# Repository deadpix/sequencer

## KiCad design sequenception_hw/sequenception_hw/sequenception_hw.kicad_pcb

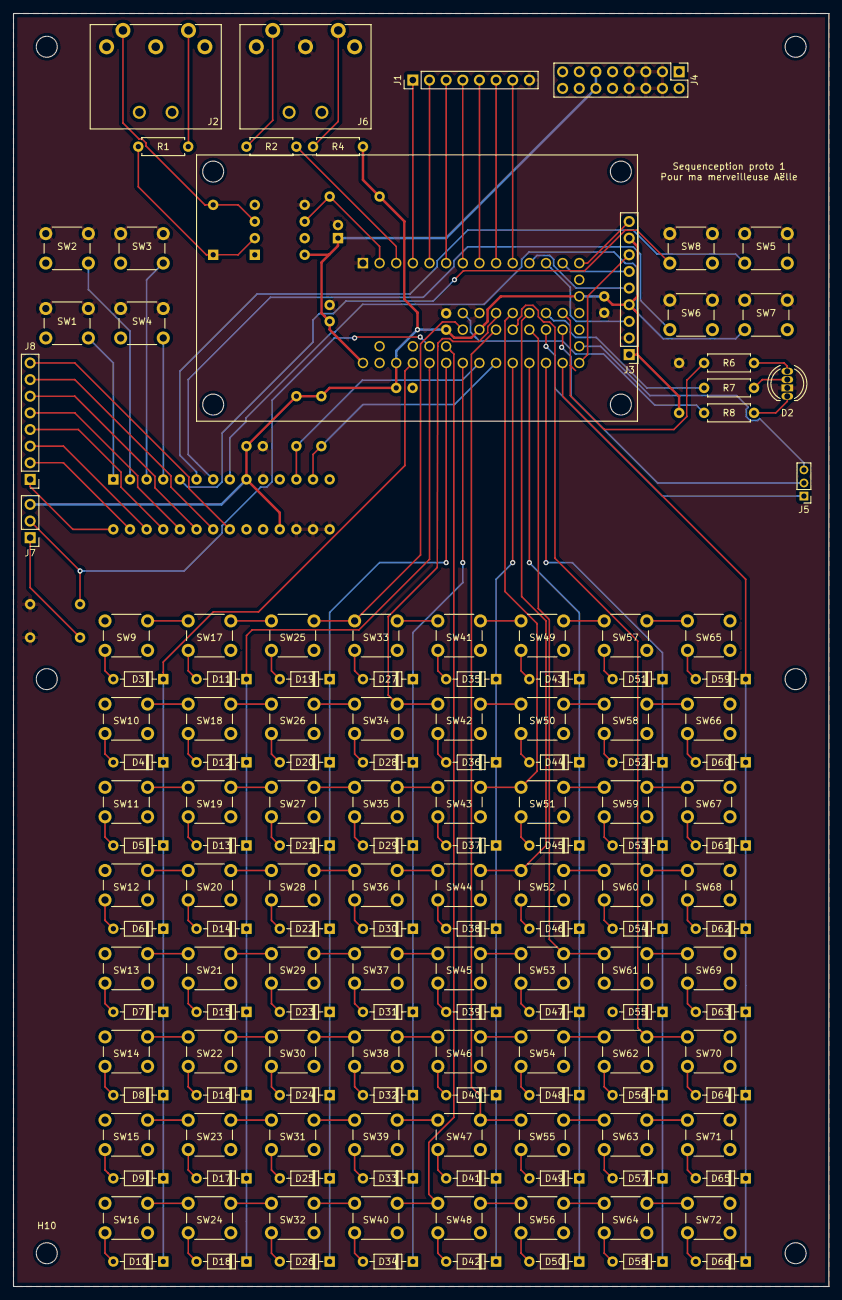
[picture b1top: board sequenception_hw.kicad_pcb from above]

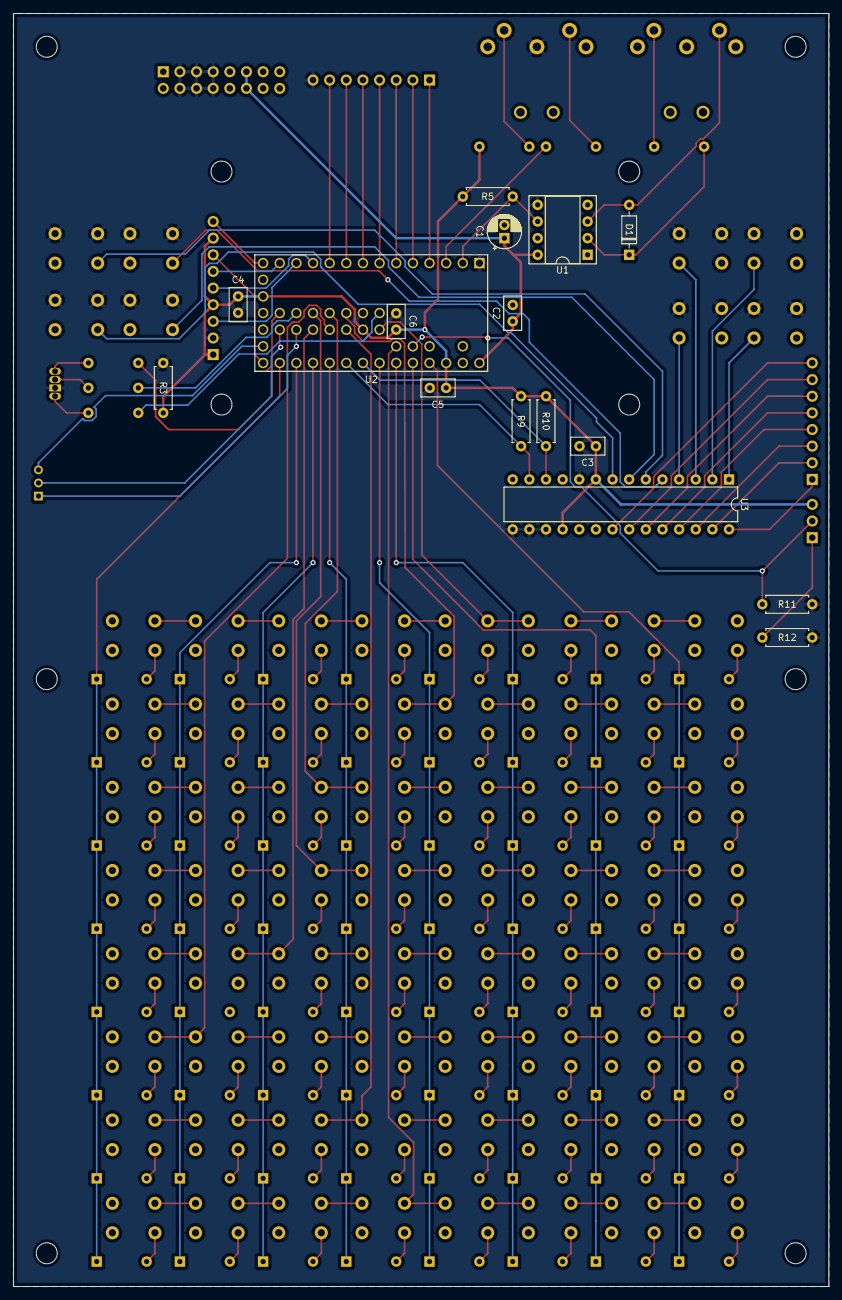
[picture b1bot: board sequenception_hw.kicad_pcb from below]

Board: 2 copper layers, 124.5 x 194.3 mm, 177 parts (16 on the bottom side), 131 nets.

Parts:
C1: 0.1uF; CP_Radial_D5.0mm_P2.00mm
C2, C3, C4, C5, C6: 0.1uF; C_Disc_D5.0mm_W2.5mm_P2.50mm
D1: 1N4148; D_DO-35_SOD27_P7.62mm_Horizontal
D2: LED_CRGB; LED_D5.0mm-4_RGB_common-cathode
D3, D4, D5, D6, D7, D8, D9, D10, D11, D12, D13, D14, D15, D16, D17, D18, D19, D20, D21, D22, D23, D24, D25, D26, D27, D28, D29, D30, D31, D32, D33, D34, D35, D36, D37, D38, D39, D40, D41, D42, D43, D44, D45, D46, D47, D48, D49, D50, D51, D52, D53, D54, D55, D56, D57, D58, D59, D60, D61, D62, D63, D64, D65, D66: D; D_DO-35_SOD27_P7.62mm_Horizontal
H1, H2, H3, H4, H5, H6, H7, H8, H9, H10: MountingHole; MountingHole_3.2mm_M3
J1, J8: Conn_01x08_Male; PinHeader_1x08_P2.54mm_Vertical
J2: MIDI_IN; SDS-50J
J3: Conn_01x09_Female; PinHeader_1x09_P2.54mm_Vertical
J4: Conn_02x08_Odd_Even; PinHeader_2x08_P2.54mm_Vertical
J5: Conn_01x03_Male; PinHeader_1x03_P2.00mm_Vertical
J6: MIDI_OUT; SDS-50J
J7: SOFTPOT_CONN; PinHeader_1x03_P2.54mm_Vertical
R1: 220; R_Axial_DIN0207_L6.3mm_D2.5mm_P7.62mm_Horizontal
R2, R4, R6, R7, R8: 47; R_Axial_DIN0207_L6.3mm_D2.5mm_P7.62mm_Horizontal
R3: 100; R_Axial_DIN0207_L6.3mm_D2.5mm_P7.62mm_Horizontal
R5: 470; R_Axial_DIN0207_L6.3mm_D2.5mm_P7.62mm_Horizontal
R9, R10: 4.7K; R_Axial_DIN0207_L6.3mm_D2.5mm_P7.62mm_Horizontal
R11, R12: R; R_Axial_DIN0207_L6.3mm_D2.5mm_P7.62mm_Horizontal
SW1, SW2, SW3, SW4, SW5, SW6, SW7, SW8, SW9, SW10, SW11, SW12, SW13, SW14, SW15, SW16, SW17, SW18, SW19, SW20, SW21, SW22, SW23, SW24, SW25, SW26, SW27, SW28, SW29, SW30, SW31, SW32, SW33, SW34, SW35, SW36, SW37, SW38, SW39, SW40, SW41, SW42, SW43, SW44, SW45, SW46, SW47, SW48, SW49, SW50, SW51, SW52, SW53, SW54, SW55, SW56, SW57, SW58, SW59, SW60, SW61, SW62, SW63, SW64, SW65, SW66, SW67, SW68, SW69, SW70, SW71, SW72: SW_Push; SW_PUSH_6mm
U1: 6N138; DIP-8_W7.62mm_Socket
U2: Teensy3.2-teensy; Teensy_32_test
U3: MCP23017_SP; DIP-28_W7.62mm

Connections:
+3V3: C3.1, C4.1, C5.1, C6.1, J3.1, J3.4, J3.8, J7.3, R3.2, R4.1, R5.2, R9.2, R10.1, U2.16, U2.31, U2.46, U3.9, U3.18
+5V: C1.1, C2.1, J4.11, J4.12, U1.8, U2.33
/BLUE: R6.2, U2.44
/DC_RS: J3.5, U2.11
/GPA0: J8.8, U3.21
/GPA1: J8.7, U3.22
/GPA2: J8.6, U3.23
/GPA3: J8.5, U3.24
/GPA4: J8.4, U3.25
/GPA5: J8.3, U3.26
/GPA6: J8.2, U3.27
/GPA7: J8.1, U3.28
/GREEN: R7.2, U2.43
/I2C_CLK: R10.2, U2.26, U3.12
/I2C_DATA: R9.1, U2.25, U3.13
/MAT_COL_0: D3.1, D4.1, D5.1, D6.1, D7.1, D8.1, D9.1, D10.1, U2.30
/MAT_COL_1: D11.1, D12.1, D13.1, D14.1, D15.1, D16.1, D17.1, D18.1, U2.29
/MAT_COL_2: D19.1, D20.1, D21.1, D22.1, D23.1, D24.1, D25.1, D26.1, U2.28
/MAT_COL_3: D27.1, D28.1, D29.1, D30.1, D31.1, D32.1, D33.1, D34.1, U2.27
/MAT_COL_4: D35.1, D36.1, D37.1, D38.1, D39.1, D40.1, D41.1, D42.1, U2.24
/MAT_COL_5: D43.1, D44.1, D45.1, D46.1, D47.1, D48.1, D49.1, D50.1, U2.23
/MAT_COL_6: D51.1, D52.1, D53.1, D54.1, D55.1, D56.1, D57.1, D58.1, U2.22
/MAT_COL_7: D59.1, D60.1, D61.1, D62.1, D63.1, D64.1, D65.1, D66.1, U2.21
/MAT_ROW_0: SW9.1, SW17.1, SW25.1, SW33.1, SW41.1, SW49.1, SW57.1, SW65.1, U2.51
/MAT_ROW_1: SW10.1, SW18.1, SW26.1, SW34.1, SW42.1, SW50.1, SW58.1, SW66.1, U2.40
/MAT_ROW_2: SW11.1, SW19.1, SW27.1, SW35.1, SW43.1, SW51.1, SW59.1, SW67.1, U2.41
/MAT_ROW_3: SW12.1, SW20.1, SW28.1, SW36.1, SW44.1, SW52.1, SW60.1, SW68.1, U2.42
/MAT_ROW_4: SW13.1, SW21.1, SW29.1, SW37.1, SW45.1, SW53.1, SW61.1, SW69.1, U2.48
/MAT_ROW_5: SW14.1, SW22.1, SW30.1, SW38.1, SW46.1, SW54.1, SW62.1, SW70.1, U2.49
/MAT_ROW_6: SW15.1, SW23.1, SW31.1, SW39.1, SW47.1, SW55.1, SW63.1, SW71.1, U2.50
/MAT_ROW_7: SW16.1, SW24.1, SW32.1, SW40.1, SW48.1, SW56.1, SW64.1, SW72.1, U2.37
/PIN2: J1.1, U2.4
/PIN3: J1.2, U2.5
/PIN4: J1.3, U2.6
/PIN5: J1.4, U2.7
/PIN6: J1.5, U2.8
/PIN7: J1.6, U2.9
/PIN8: J1.7, U2.10
/PIN10: J5.3, U2.19
/PIN11: J5.1, U2.47
/PIN12: J5.2, U2.45
/RED: R8.2, U2.38
/SP: J7.2, R11.1, U2.36
/SPI_CLK: J3.7, U2.20
/SPI_CS: J3.3, U2.12
/SPI_DIN: J3.9, U2.14
/SPI_DOUT: J3.6, U2.13
GND: C1.2, C2.2, C3.2, C4.2, C5.2, C6.2, D2.1, J1.8, J3.2, J4.3, J4.4, J4.5, J4.6, J4.7, J4.8, J6.2, R3.1, R11.2, R12.2, SW1.2, SW2.2, SW3.2, SW4.2, SW5.2, SW6.2, SW7.2, SW8.2, U1.5, U2.1, U2.17, U2.39, U3.10, U3.15, U3.16, U3.17
unnamed: D1.1, R1.1, U1.2
unnamed: D1.2, J2.5, U1.3
unnamed: D2.2, R8.1
unnamed: D2.3, R7.1
unnamed: D2.4, R6.1
unnamed: D3.2, SW9.2
unnamed: D4.2, SW10.2
unnamed: D5.2, SW11.2
unnamed: D6.2, SW12.2
unnamed: D7.2, SW13.2
unnamed: D8.2, SW14.2
unnamed: D9.2, SW15.2
unnamed: D10.2, SW16.2
unnamed: D11.2, SW17.2
unnamed: D12.2, SW18.2
unnamed: D13.2, SW19.2
unnamed: D14.2, SW20.2
unnamed: D15.2, SW21.2
unnamed: D16.2, SW22.2
unnamed: D17.2, SW23.2
unnamed: D18.2, SW24.2
unnamed: D19.2, SW25.2
unnamed: D20.2, SW26.2
unnamed: D21.2, SW27.2
unnamed: D22.2, SW28.2
unnamed: D23.2, SW29.2
unnamed: D24.2, SW30.2
unnamed: D25.2, SW31.2
unnamed: D26.2, SW32.2
unnamed: D27.2, SW33.2
unnamed: D28.2, SW34.2
unnamed: D29.2, SW35.2
unnamed: D30.2, SW36.2
unnamed: D31.2, SW37.2
unnamed: D32.2, SW38.2
unnamed: D33.2, SW39.2
unnamed: D34.2, SW40.2
unnamed: D35.2, SW41.2
unnamed: D36.2, SW42.2
unnamed: D37.2, SW43.2
unnamed: D38.2, SW44.2
unnamed: D39.2, SW45.2
unnamed: D40.2, SW46.2
unnamed: D41.2, SW47.2
unnamed: D42.2, SW48.2
unnamed: D43.2, SW49.2
unnamed: D44.2, SW50.2
unnamed: D45.2, SW51.2
unnamed: D46.2, SW52.2
unnamed: D47.2, SW53.2
unnamed: D48.2, SW54.2
unnamed: D49.2, SW55.2
unnamed: D50.2, SW56.2
unnamed: D51.2, SW57.2
unnamed: D52.2, SW58.2
unnamed: D53.2, SW59.2
unnamed: D54.2, SW60.2
unnamed: D55.2, SW61.2
unnamed: D56.2, SW62.2
unnamed: D57.2, SW63.2
unnamed: D58.2, SW64.2
unnamed: D59.2, SW65.2
unnamed: D60.2, SW66.2
unnamed: D61.2, SW67.2
unnamed: D62.2, SW68.2
unnamed: D63.2, SW69.2
unnamed: D64.2, SW70.2
unnamed: D65.2, SW71.2
unnamed: D66.2, SW72.2
unnamed: J2.4, R1.2
unnamed: J6.4, R4.2
unnamed: J6.5, R2.2
unnamed: J7.1, R12.1
unnamed: R2.1, U2.3
unnamed: R5.1, U1.6, U2.2
unnamed: SW1.1, U3.1
unnamed: SW2.1, U3.2
unnamed: SW3.1, U3.3
unnamed: SW4.1, U3.4
unnamed: SW5.1, U3.6
unnamed: SW6.1, U3.7
unnamed: SW7.1, U3.8
unnamed: SW8.1, U3.5

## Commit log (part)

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2016-12-27 remove external MIDI library
2017-02-03 create library folder and clock class used in sequencer and time related operation
2017-02-03 renamed clock.* into clk.*
2017-02-03 add gate class for euroduino sigan program (does not compile yet)
2017-02-05 dev on sigan sketch (does not compile yet)
2017-02-10 update euroduino sigan, might not compile
2017-02-13 update euroduino sketch: might not compile
2017-02-23 modify sigan, does not compile
2017-02-26 time reverse gate and random ok
2017-03-10 try to fix external clock (compilation not tested)
2017-03-13 ext clock ok, but master does not output correctly tick (problem with master clk multiplier)
2017-03-14 add debug test
2017-03-15 ext clock seems ok with both divider and multiplier
2017-03-16 add clk trig level but not tested/compiled
2017-03-22 Fix random output: random clock was synchronized 2 times instead of 1 time per clock sync
2017-03-27 change clk function for syncing slave clock (compile but not tested)
2017-03-29 fix bug on clk gate length
2017-03-30 Add trig level to sync input (compile but not tested)
2017-03-31 code cleaning, to be tested
2017-04-04 test file for led matrix with shift register
2017-04-04 add test to shift register led matrix
2017-04-26 add static to local functions
2017-04-28 fix cv over slave clk multiplier bug (compilation not tested)
2017-05-11 Fix bugs and start refactoring (random), not tested, not compiled
2017-05-12 add MIT license and start random cv code refactoring. Not tested / not compiled.
2017-05-15 code refactoring and add comments. compile but not tested
2017-05-19 refactoring
2017-05-26 add comment for debug slv triggered clk
2017-05-28 test of shift register for leds matrix ok
2017-06-02 new arduino source for testing shift register
2017-06-12 fix compilation error
2017-06-26 fix problem on test5 and add test for LED matrix
2017-06-27 add support for btn matrix with I2C IO expander (MCP23017)
2017-07-12 H/W test on 8*4 matrix (led+btn)
2017-07-12 create new test folder for sequencer
2017-07-24 Fix attenuate CV bug (wrong variable type)
2017-07-27 Fix bug from previous commit
    + fix random CV
    + fix slace CV
    + fix the copy/paste mess from previous commit
2017-07-28 Add euroduino documentation
2017-07-30 menu btn integration
    TODO: menu button need to be integrate (end of test6.ino file)
2017-08-01 update sigan manual
2017-08-08 add bit library
2017-08-09 add clk class
2017-08-09 spilt arduino main code
    separate matrix led/btn function from arduino main code
2017-08-10 documentation for euroduino sigan prog
2017-08-13 test4 / test7 mergin
    compile but not tested
2017-08-20 button menu code
    unstable / might not compile
2017-08-22 fix
    fix compilation error of previous commit
2017-08-24 add function for getting ptr to prog class
    compile but not tested
2017-08-27 midi class / update menu callback
    + new midi class => send 24ppqn info
    + add on_push / on_release callback instead of update callback function (on release)
2017-08-30 add led animation class
    might not compile
    need to update prog class, tempo class
2017-09-01 update manual of sigan firmware
2017-09-01 fix tempo class
    compile but not tested
2017-09-03 fix tap tempo
2017-09-05 Add prototype function for eeprom saving/restore
2017-09-07 code cleaning
    status: unknown
    + compile OK
    + execute: unknown
2017-09-10 refactoring fix + midi sync
    Status:
    + exec OK
    + midi sync KO
2017-09-14 add sequencer/track class
    status:
    - compile OK
    - run ???
2017-09-20 add eeprom function, COMPILE/EXEC not tested
2017-09-28 midi step sequencer
    + GUI ok
    + midi out ko
    + midi seq menu ko
2017-10-26 hw configuration update
    update for using new matrix led H/W
2017-11-07 Fix midi seq
    Fix midi seq and midi controller
2017-11-16 Add GUI class for handling oled
    Does not compile, error with static class GUI
2017-11-17 update oled gui, compile but not tested
2017-11-23 test8: start code refactoring
2017-11-23 try refactoring code
2017-11-25 create parameter setting for test7, refactoring test8
    test7
    compile OK
    exec KO
    test8 KO
2017-11-26 Fix bug in sequencer param
    Status;
    - compile OK
    - exec OK
2017-11-27 Add call to oled gui during parameters selection
2017-11-27 add oled GUI call in sequencer function
2017-11-30 add step counter function
    function step counter fix the limit of a step in track: only function prototype
    status;
    - compile OK
    - exec: ?
2017-11-30 miising file from last merge
2017-12-12 Add cscope support (vim/cscope) and rename class fct_step_count in fct_loop_setting (compile:ok exec:???)
2017-12-12 modify update_ui function parameeters to get master clock info (compile: OK exec: ???)
2017-12-13 add clock divider UI in sequencer parameter (compile: ??? exec: ???)
2017-12-14 Add clock multiplier UI in sequencer parameter (compile: OK exec: ???)
2018-01-11 Add h/w errata
2018-01-14 ake gen_scope.sh executable
2018-01-18 fix some parameters bug. Add control on param button and menu button when a matrix button is pushed. Compile OK exec OK.
2018-01-22 Fix LED gui but method with linked list takes too much dynamic memory: need to do it statically
2018-01-23 Change set_n_save / clr_n_restore function for less pressure on dynamic memory. Compile OK exec OK
2018-01-25 add ply/stop function in menu. compile OK exec ??
2018-02-01 Add long push handler with blinking led
2018-02-08 add linked step. Compile OK, exec KO
2018-02-09 change linked step algo. Compile ?? Exec ??
2018-02-14 Partial fix for linked step. Need to handle case when linking step inside linked stepgit stage midi.ino src/sequencer/fct_step.cpp step.cpp step.h ! compile OK exec OK
2018-02-22 Change clock divide/multiply method. Compile OK exec ??
2018-02-22 Fix ratio clock. Compile OK exec OK
2018-02-22 add pointer to next step in class step. Compile OK exec OK
2018-02-23 add clk pointer in step class. Compile ??? exec ???
2018-03-04 Fix loop length setting. Compile OK exec OK
2018-03-06 shift step function. Compile ?? Exec ??
2018-03-06 sub track creation. clear_n_restore does not work well... Compile OK exec KO
2018-03-08 clock evaluation need to be changed. Compile OK exec KO
2018-03-11 partial refactoring of track class. Compile OK exec OK
2018-03-13 add trace for debugging subtrack function. Compile ?? exec ko
2018-03-13 partial fix for sub track functions
2018-03-16 update clock track sync. Compile KO exec KO
2018-03-16 Fix function that add subtrack. Compile OK exec OK
2018-04-27 add prototype of sequencer emulator
2018-04-29 create refactoring folder for test7. Compile ?? Exec ??
2018-04-30 Add elapsedMillis class in sequencer emulator
2018-05-02 Fix compilation error, change Main.* to sequenception.*. Compile KO
2018-05-03 change sequenception class to static class
2018-05-14 add conversion function for led_matrix in sequencer emulator. compile ?? exec ??
2018-05-14 add led_matrix file in seq_emulator
2018-05-19 add converter for led matrix value. Compile OK exec OK
2018-05-19 refactoring. compile OK exec ??
2018-05-20 remove debug print (Serial.print(...)), need to create special lib. change boolean to bool. Compile OK exec ??
2018-05-20 Remove Makefile in seq_emulator ==> generated with $ qmake seq.pro
2018-05-25 add long push handler and menu/param button handler. compile ?? exec ??
2018-05-27 add debug class
2018-06-02 remove cscope files
2018-06-02 Fix bug on emulator
2018-06-03 fix bug. Compile OK exec OK
2018-06-03 add Qt creator project
2018-06-05 sequenception emulator: GUI fix
2018-06-07 add label for oled labels
2018-06-08 update Bounce_array class: add variable to callback function
2018-06-08 update Bounce_array class. Compile ok exec ??
2018-06-15 seq_emu2/seq_emu2/mainwindow.cpp
2018-06-20 Fix various bugs
2018-06-25 Fix bug in sequencer param
2018-06-27 forbid access to set_led_x(...) and clr_led_x(...) methods in class led_matrix. Add UNUSED macro for removing compilation warning.
2018-06-29 add signature change visualization. Compile OK exec KO
2018-10-01 Change clock visual feedback
2018-10-03 Fix compilation error. Compile OK exec KO
2018-10-05 Fix compilation warning and unexpected gui crash. Compile OK exec ??
2018-10-05 Fix some GUI bugs. TODO: fix loop setting
2018-10-07 Fix loop setting GUI (only GUI). Compile OK exec KO
2018-10-09 add sub sequence functionality. Compile OK exec KO
2018-10-10 Fix creation of sub-steps. Compile OK exec OK
2018-10-11 Add clock visual feedback on several subseq. compile OK exec OK
2018-10-12 add show function for subsequence visualisation => might have some problem with deletion of unused steps. Compile OK exec KO
2018-10-15 Fix GUI. Might be more bug related to subseq. Compile OK exec OK
2018-10-16 Fix GUI problem. clock calculation for sub step does not work
2018-10-28 fix bugs related to clock calculation
2018-12-29 add h/w support for adafruit neotrellis
2018-12-29 remove vi backup file
2019-01-08 Add functions for neotrellis led / btn matrix. Compile KO
2019-01-08 Fix some compilation errors. Compile KO
2019-01-09 Fix compilation error. compile OK exec KO.
2019-01-10 Add support functions for neotrellis hw. Compile KO
2019-01-15 Add support for matrix of command buttons
2019-01-16 Add button handlers for the cmd matrix. Compile ?? exec ??
2019-01-16 Fix use of Wire1 on NeoTrellis. Compile KO exec KO
2019-01-17 Fix compilation error and update cmd button matrix functions
2019-01-17 Add trace for debugging. Compike OK
2019-01-21 fix cmd button matrix. menu button OK param button KO
2019-01-22 Fix crash when pushing cmd parameter button. Compile OK exec ??
2019-01-23 Fix param button bug. Fix strange colors of neotrellis matrix led. Compile OK exec OK
2019-01-24 code refactoring: move track check event in ISR.Compile OK exc OK
2019-01-25 create event lists to execute GUI related functions. Compile OK exec ??
2019-01-26 Fix UI issues with neotrellis HW. Compile OK exec OK
2019-01-30 add interrupt barrier to avoid data corruption during interupt servicing but might not be enough. shared variables between ISR and normal code has to be volatile
2019-01-30 Change IRQ time to 1ms but unstable... Fix tempo gui
2019-01-31 add test on event queue to limit the number of elements
2019-02-01 Fix default note assignment for each track
2019-02-02 add midi controller function. Compile ?? exec ??
2019-02-07 Fix GUI freeze due to heap explosion with uncontrolled creation of event. Keyboard controller KO. Compile OK exec OK
2019-02-08 Fix GUI bug of keybord display in midi controller prog
2019-02-10 Fix long pushed callback function with neotrellis hw. Compile OK exec OK
2019-02-11 fix keyboard button layout. Add parameter class to midi controller. Fix crash when pushing param button with prog without param
2019-02-12 Fix step display of midi sequencer when playing
2019-02-12 fix keyboard layout and midi note
2019-02-13 Change midi controller class to have MATRIX_NR_COL midi configuration
2019-02-15 Fix compilation error. Compile OK exec OK
2019-02-18 Add track coloration. Need to add step coloration. Compile OK exec OK
2019-02-21 add drum layout for midi controller
2019-02-23 update sequence loop
2019-03-05 update loop setting GUI. Compile KO
2019-03-10 Fix compilation error of previous commit. Compile OK exec ???
2019-03-12 Fix loop setting -> set_last_in_loop / set_first_in_loop functions has to be fixed. Compile KO
2019-03-15 Fix setting of track looping points. To be tested
2019-03-16 Fix function that set start and end points of a loop. Not tested with sub-sequencers. Compile OK exec OK
2019-03-27 remove unused functions
2019-03-28 test shift register
2019-04-03 move interrupts.h in arduino default library folders
2019-04-28 Fix shift register drivers
2019-12-20 add serialization function
2020-01-22 improve stability of save / load sequence function (serialization / deserialization)
2020-02-18 Add new matrix H/W
2020-03-24 Add tree visualization in simulator
2020-04-03 Add blinking class to support led blink. Add normalization function
2020-05-29 add sequenception HW
2020-08-23 cleanup repo
2020-08-23 rename seq_emu2 in simulator
2020-08-23 change debouncing of button matrix. Does not compile...
2020-08-25 Add file relative to compilation issue
